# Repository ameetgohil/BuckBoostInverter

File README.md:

# BuckBoostInverter
Buck Boost Inverter ouputs -5.5V with +15V input

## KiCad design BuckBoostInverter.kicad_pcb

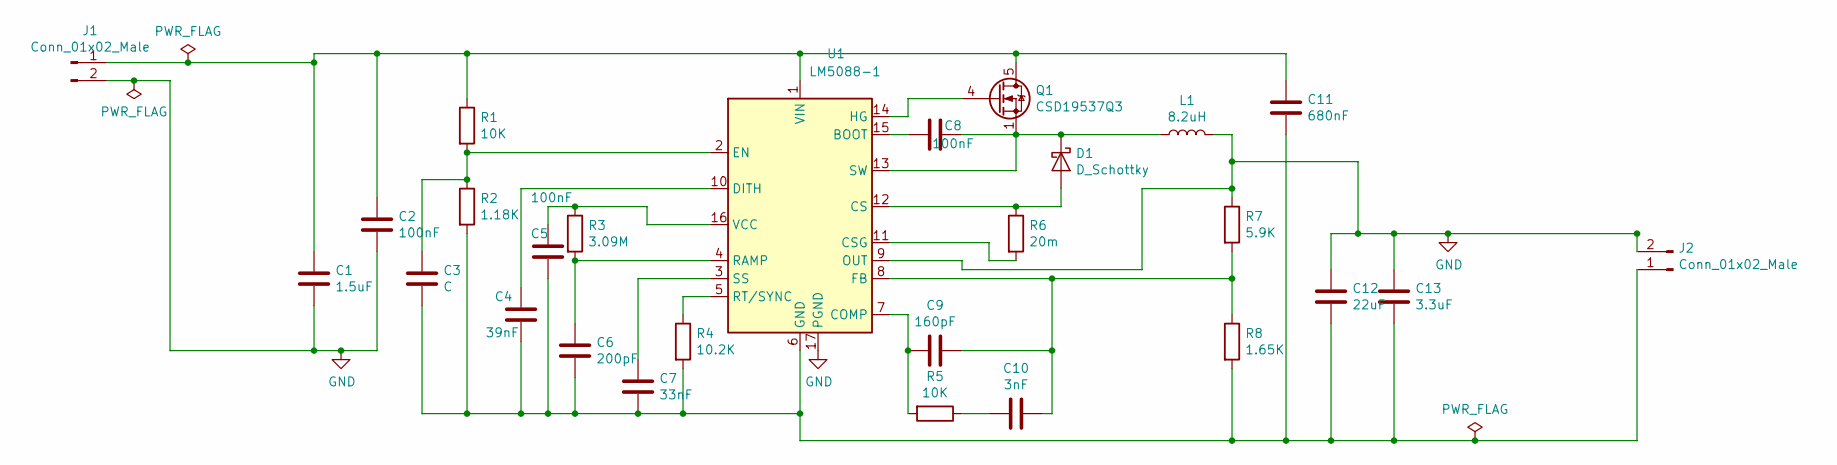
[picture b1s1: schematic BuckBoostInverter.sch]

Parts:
C1: 1.5uF; C_0603_1608Metric_Pad1.05x0.95mm_HandSolder
C2, C8: 100nF; C_0805_2012Metric_Pad1.15x1.40mm_HandSolder
C3: C; C_0402_1005Metric
C4: 39nF; C_0402_1005Metric
C5: 100nF; C_0603_1608Metric_Pad1.05x0.95mm_HandSolder
C6: 200pF; C_0402_1005Metric
C7: 33nF; C_0402_1005Metric
C9: 160pF; C_0805_2012Metric_Pad1.15x1.40mm_HandSolder
C10: 3nF; C_0603_1608Metric_Pad1.05x0.95mm_HandSolder
C11: 680nF; C_0805_2012Metric_Pad1.15x1.40mm_HandSolder
C12: 22uF; C_0805_2012Metric_Pad1.15x1.40mm_HandSolder
C13: 3.3uF; C_0805_2012Metric_Pad1.15x1.40mm_HandSolder
D1: D_Schottky; VS-50WQ10FNTR-M3
J1, J2: Conn_01x02_Male; PowerPads
L1: 8.2uH; L_12x12mm_H6mm
Q1: CSD19537Q3; VSON-8_3.3x3.3mm_P0.65mm_NexFET
R1, R5: 10K; R_0402_1005Metric
R2: 1.18K; R_0402_1005Metric
R3: 3.09M; R_0402_1005Metric
R4: 10.2K; R_0402_1005Metric
R6: 20m; R_1206_3216Metric_Pad1.42x1.75mm_HandSolder
R7: 5.9K; R_0402_1005Metric
R8: 1.65K; R_0402_1005Metric
U1: LM5088-1; HTSSOP-16-1EP_4.4x5mm_P0.65mm_EP3.4x5mm_Mask3x3mm_ThermalVi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

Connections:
GND: C1.2, C2.2, C12.1, C13.1, J1.2, J2.2, L1.2, R7.1, U1.9 (OUT), U1.17 (PGND)
unnamed: C1.1, C2.1, C11.1, J1.1, Q1.5 (D), R1.1, U1.1 (VIN)
unnamed: C3.1, R1.2, R2.1, U1.2 (EN)
unnamed: C4.1, U1.10 (DITH)
unnamed: C5.1, R3.1, U1.16 (VCC)
unnamed: C6.1, R3.2, U1.4 (RAMP)
unnamed: C7.1, U1.3 (SS)
unnamed: C8.1, D1.1 (K), L1.1, Q1.1 (S), Q1.2 (S), Q1.3 (S), U1.13 (SW)
unnamed: C8.2, U1.15 (BOOT)
unnamed: C9.2, R5.2, U1.7 (COMP)
unnamed: C9.1, C10.1, R7.2, R8.1, U1.8 (FB)
unnamed: C10.2, R5.1
unnamed: C3.2, C4.2, C5.2, C6.2, C7.2, C11.2, C12.2, C13.2, J2.1, R2.2, R4.2, R8.2, U1.6 (GND)
unnamed: D1.2 (A), R6.1, U1.12 (CS)
unnamed: Q1.4 (G), U1.14 (HG)
unnamed: R4.1, U1.5 (RT/SYNC)
unnamed: R6.2, U1.11 (CSG)

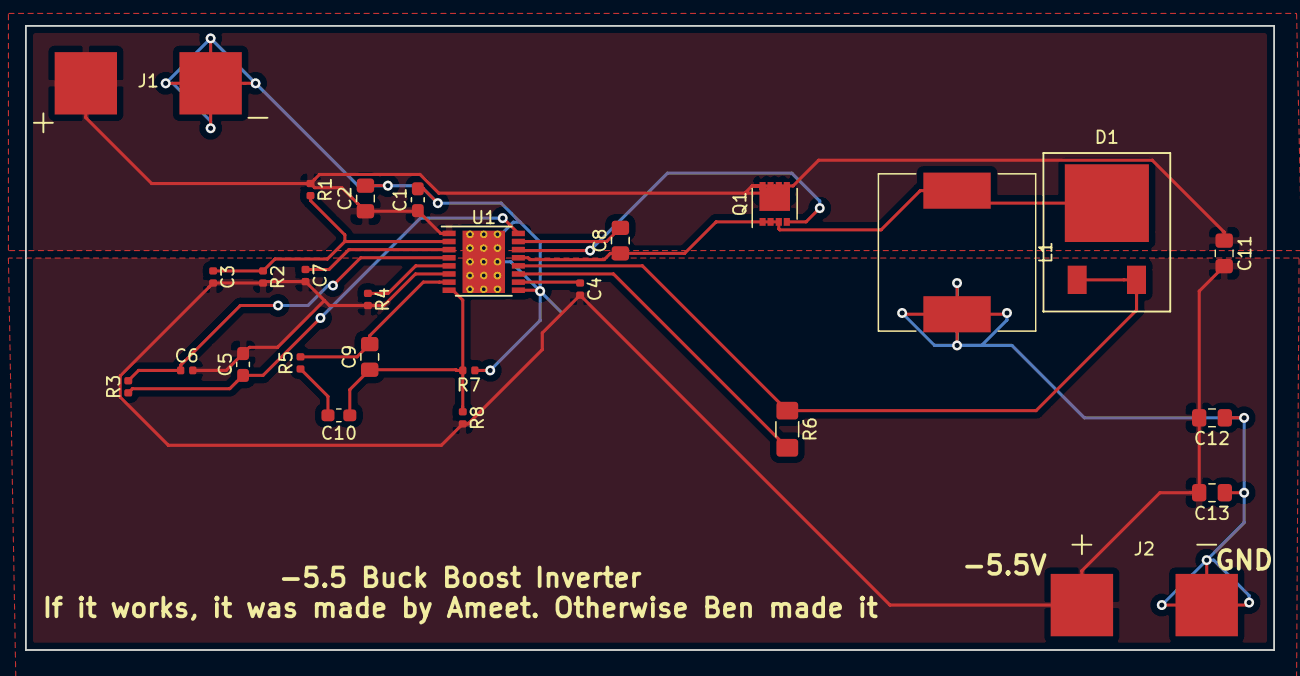
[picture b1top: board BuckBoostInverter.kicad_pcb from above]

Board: 2 copper layers, 100.0 x 50.0 mm, 27 parts (0 on the bottom side), 17 nets.

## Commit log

2019-03-21 init project
2019-03-21 add gitignore
2019-04-11 add schematic
2019-04-11 add footprint and assign footprints to parts
2019-04-11 import netlist, relayout rats nest
2019-04-12 finish layout, generate gerbers
